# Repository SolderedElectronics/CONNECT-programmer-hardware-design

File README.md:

# CONNECT programmer Hardware Design

## About the Product

|  |
| :----------------------------------------------------------: |
| [Buy CONNECT programmer](https://www.solde.red/333073) |

CONNECT programmer is designed to allow extremely simple programming of boards based on ESP8266 and ESP32 microcontrollers. It contains all the necessary electronics and logic so that programming can be done by plugging USB cable into CONNECT programmer and connecting CONNECT programmer to the programming header. Electronics that take care of timing and signal sequence are also on board, so it puts the ESP uC into bootloader mode.

ESP programming header can be found boards made by Soldered based on ESP8266 or ESP32 microcontrollers that do not have a USB-UART converter, but this programmer can be used for any other ESP32 / ESP8266 board as well.

---

## Repository Contents

This repository contains all design files for CONNECT programmer, organized as follows:

- **`CAD` folder**: Contains KiCAD design files, including:
  - Schematics
  - PCB layout
  - Panel PCB layout
  - Source 3D files in Fusion360, if any
  - All files are sorted by version with a detailed change log.
- **`OUTPUTS` folder**: Includes all production-ready files, such as:
  - Bill of Materials (BOM) and interactive BOM (iBOM)
  - PDF versions of schematics
  - 3D `.step` file of the board
  - 3D-printable models
  - Gerber files for PCB manufacturing
  - Image of the pinout of the board
  - Product image
  - Compliance, legal and generic sales documents

Refer to the `Change Log` in the CAD folder for details about updates between versions.

---

## Learn More About the Product

Beyond the repository, explore the following resources:

### Soldered Verify

The **Soldered Verify** system ensures every board you purchase from Soldered is fully functional. It also provides access to exclusive test data for your product. To get started, find the unique Soldered Verify ID on your product's packaging and enter the ID on the [Soldered Verify page](https://soldered.com/verify/) to access test results and additional product details.

### Soldered Community

Soldered Community is your go-to place for technical support. Our engineers track and answer all questions posted there, and it’s a great space for the maker community. Get answers to your questions and solutions for your challenges at [Soldered Community](https://soldered.com/community).

### solde.red

solde.red is an ultimate URL shortener and information hub. Access it by typing solde.red/ followed by your product SKU, e.g., [solde.red/333000](https://solde.red/333000), to find getting-started guides, datasheets, open-source hardware and software files, certifications, images, pinouts, and more. Read more about the shortener [here](https://solde.red/info/).

---

## Contributing

Contributions are welcome! Here’s how you can get involved:

- Submit pull requests to enhance the design or fix issues.
- Report bugs or problems by opening an issue.

We encourage community collaboration to make this product even better.

---

## About Soldered

[Soldered for Makers](https://soldered.com) specializes in designing and manufacturing electronic products tailored for enthusiasts, ranging from hobbyists to professionals. Our portfolio includes electronic boards, sensors, and actuators that are widely utilized in fields such as microelectronics, mechatronics, robotics, programming, and IoT. Every product we offer is designed in-house and built upon open-source hardware and software platforms. Proudly certified and manufactured within the European Union, our catalog likely includes the product you need for your project.

We complement these products with comprehensive tutorials and manuals, product descriptions, schematics, programming codes, and project examples. Our round-the-clock [customer and technical support](https://soldered.com/community) is available for all our products, irrespective of the sales channel. Soldered’s success and services reflect our maker community’s unwavering [trust](https://www.trustpilot.com/review/soldered.com), for which we are deeply grateful. Join our community and create using Soldered products.

---

## License

All Soldered open-source hardware (OSH) is under The TAPR Open Hardware License. Read more in the LICENSE file located in this repository.

**Disclaimer:**

No warranty - all designs in this repository are distributed in the hope that they will be useful, but without any warranty. They are provided "AS IS", therefore without warranty of any kind, either expressed or implied. The entire quality and performance of what you do with the contents of this repository are your responsibility. In no event Soldered Electronics will be liable for your damages, or losses, including any general, special, incidental, or consequential damage arising out of the use or inability to use the contents of this repository. 

---

## Have fun!

Thank you for your support from your fellow makers at Soldered Electronics.

Happy Making!

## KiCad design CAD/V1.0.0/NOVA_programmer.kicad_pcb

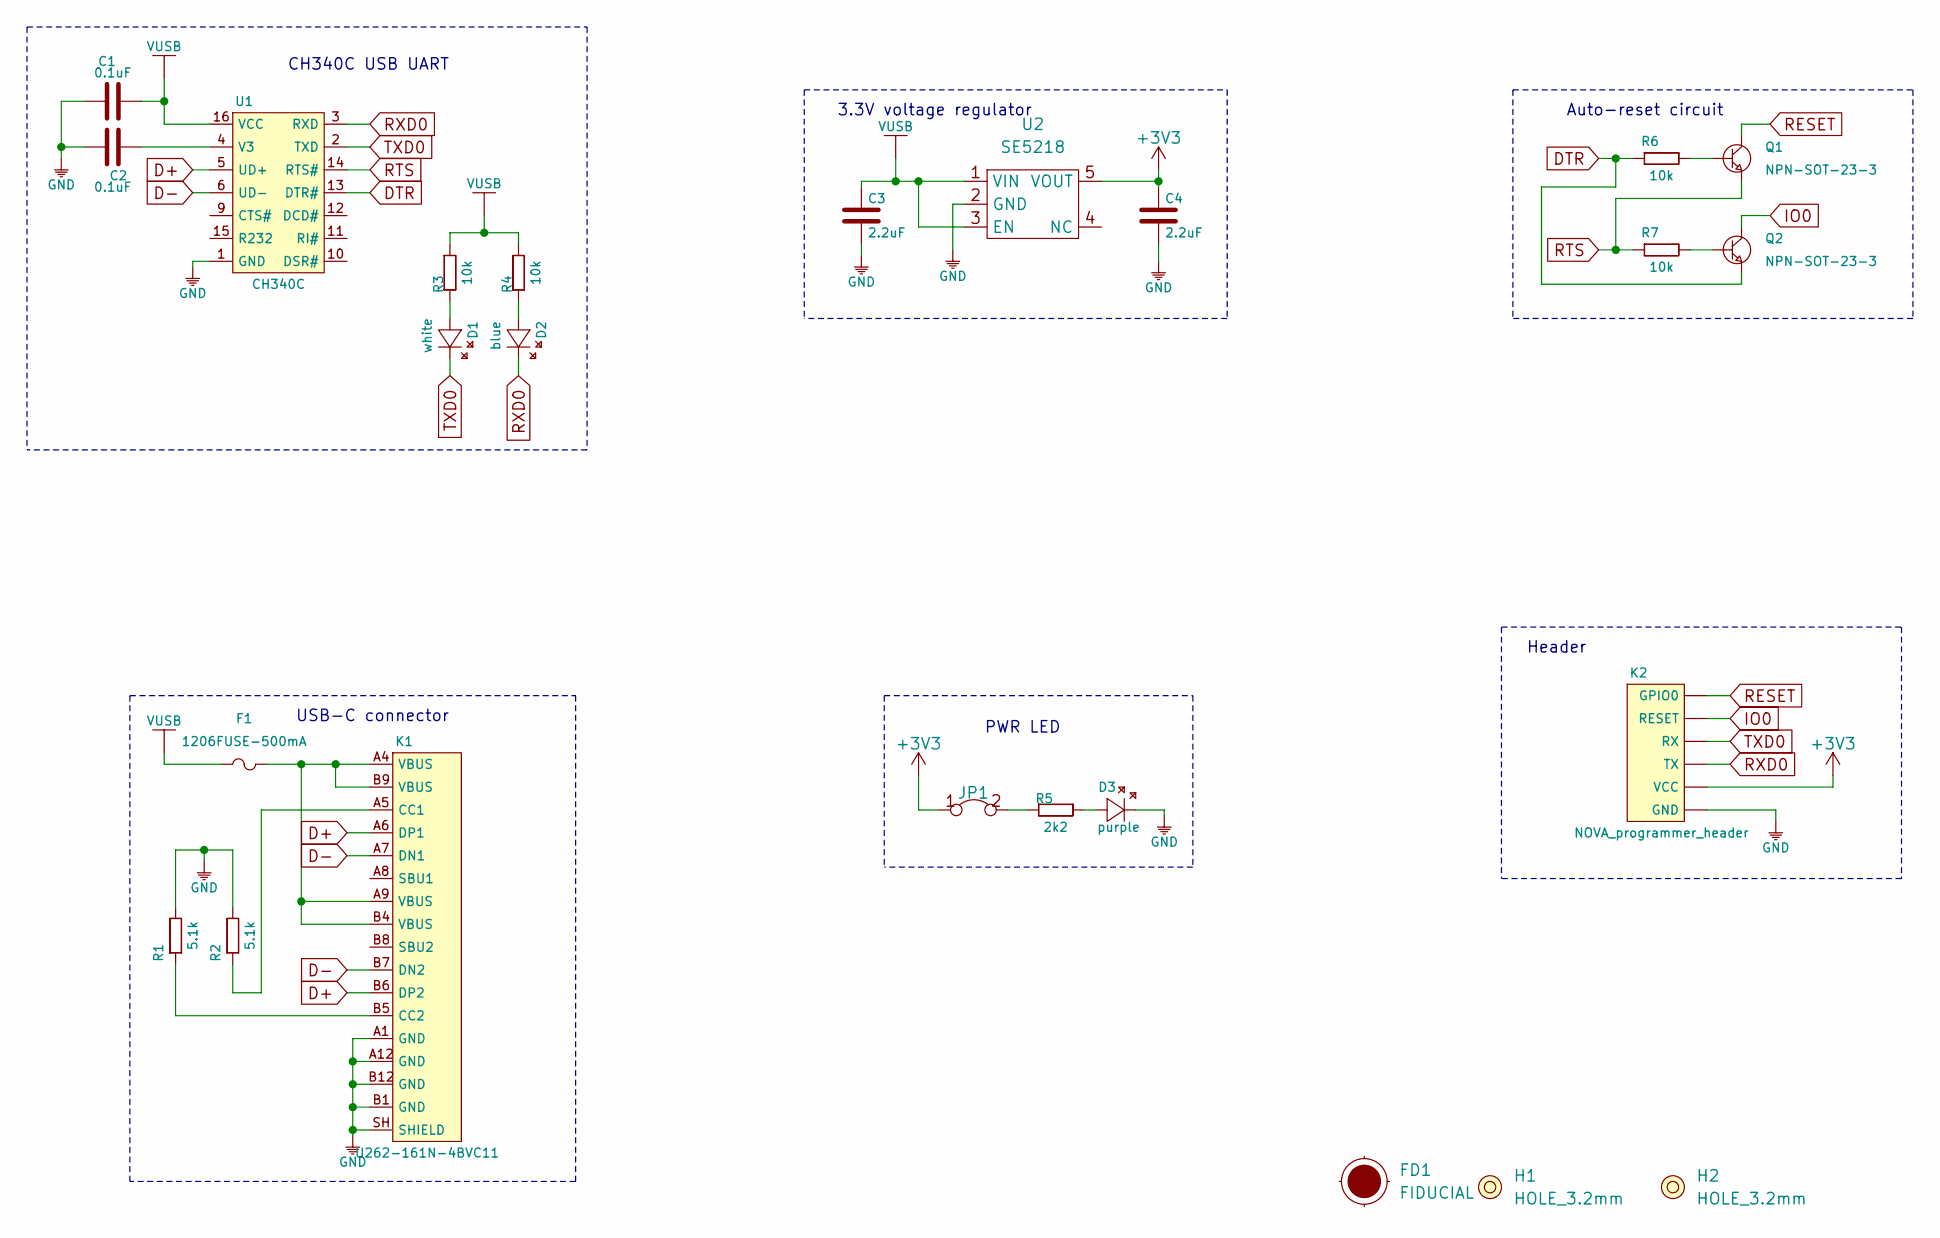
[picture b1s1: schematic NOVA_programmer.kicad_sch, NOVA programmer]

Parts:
C1, C2: 0.1uF; 0603C
C3, C4: 2.2uF; 0603C
D1: white; 0402LED
D2: blue; 0402LED
D3: purple; 0402LED
F1: 1206FUSE-500mA; 1206FUSE
FD1: FIDUCIAL; FIDUCIAL_23
H1, H2: HOLE_3.2mm
JP1: SMD-JUMPER-CONNECTED_TRACE_SLODERMASK
K1: U262-161N-4BVC11
K2: NOVA_programmer_header; HEADER_MALE_6X1
Q1, Q2: NPN-SOT-23-3; SOT-23-3
R1, R2: 5.1k; 0603R
R3, R4: 10k; 0402R
R5: 2k2; 0402R
R6, R7: 10k; 0603R
U1: CH340C; SOP-16
U2: SE5218; SOT-23-5

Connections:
+3V3: C4.2, JP1.1, K2.2 (VCC), U2.5 (VOUT)
D+: K1.A6 (DP1), K1.B6 (DP2), U1.5 (UD+)
D-: K1.A7 (DN1), K1.B7 (DN2), U1.6 (UD-)
DTR: Q2.2 (E), R6.1, U1.13 (DTR#)
GND: C1.1, C2.2, C3.1, C4.1, D3.2 (K), K1.A1 (GND), K1.A12 (GND), K1.B1 (GND), K1.B12 (GND), K1.SH (SHIELD), K2.1 (GND), R1.2, R2.2, U1.1 (GND), U2.2 (GND)
IO0: K2.5 (RESET), Q2.3 (C)
unnamed: C2.1, U1.4 (V3)
unnamed: D1.1 (A), R3.1
unnamed: D2.1 (A), R4.1
unnamed: D3.1 (A), R5.2
unnamed: F1.2, K1.A4 (VBUS), K1.A9 (VBUS), K1.B4 (VBUS), K1.B9 (VBUS)
unnamed: JP1.2, R5.1
unnamed: K1.A5 (CC1), R2.1
unnamed: K1.B5 (CC2), R1.1
unnamed: Q1.1 (B), R6.2
unnamed: Q2.1 (B), R7.2
RESET: K2.6 (GPIO0), Q1.3 (C)
RTS: Q1.2 (E), R7.1, U1.14 (RTS#)
RXD0: D2.2 (K), K2.3 (TX), U1.3 (RXD)
TXD0: D1.2 (K), K2.4 (RX), U1.2 (TXD)
VUSB: C1.2, C3.2, F1.1, R3.2, R4.2, U1.16 (VCC), U2.1 (VIN), U2.3 (EN)

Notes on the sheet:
CH340C USB UART
USB-C connector
3.3V voltage regulator
PWR LED
Header
Auto-reset circuit

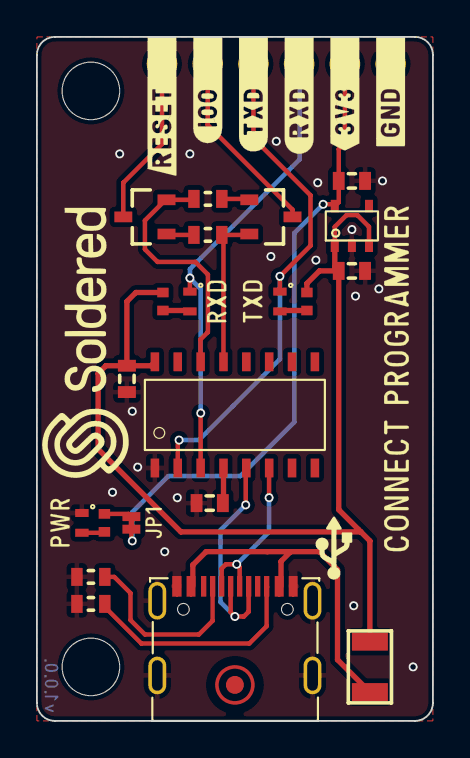
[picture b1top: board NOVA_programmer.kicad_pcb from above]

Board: 2 copper layers, 22.0 x 38.0 mm, 25 parts (1 on the bottom side), 21 nets.

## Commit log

2022-08-06 Updating open source files.
